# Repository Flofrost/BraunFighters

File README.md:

# GraphixCard

## Liscence

    This project is open source and open hardware, feel free too copy, edit, redistribute, and do whatever you want with it.
    I am not well versed in liscences, i just want to share my project.
    If you do use my project as a base for your work, please mention it.  :) 

## Info

    - Grahics card based on a ATMEGA1284.
    - Generates a PAL signal with 8 bit color.
    - Has a limited but expandable 3 voice synth (can add up to 3 voices).
    - Includes RS232 debugger (by that i mean it has an available RS232 port, it's up to anyone to do whatever).
    - C++ Code, compiled with avr-gcc and uploaded with avedude (using avriskmkii).
    - Electrical schematic made with Kicad.

## Objective

    - Make a funny retro video game.
    - This is the "video" part of the video game.
    - Make simple tools to program on the GraphiX Card.
    - Make a complete and handy instruction table.
    - Learn a ton about coding and electronics.

## About

    This project was brought to you by Florian Ballager, aka Flofrost.
## Braun Fighters

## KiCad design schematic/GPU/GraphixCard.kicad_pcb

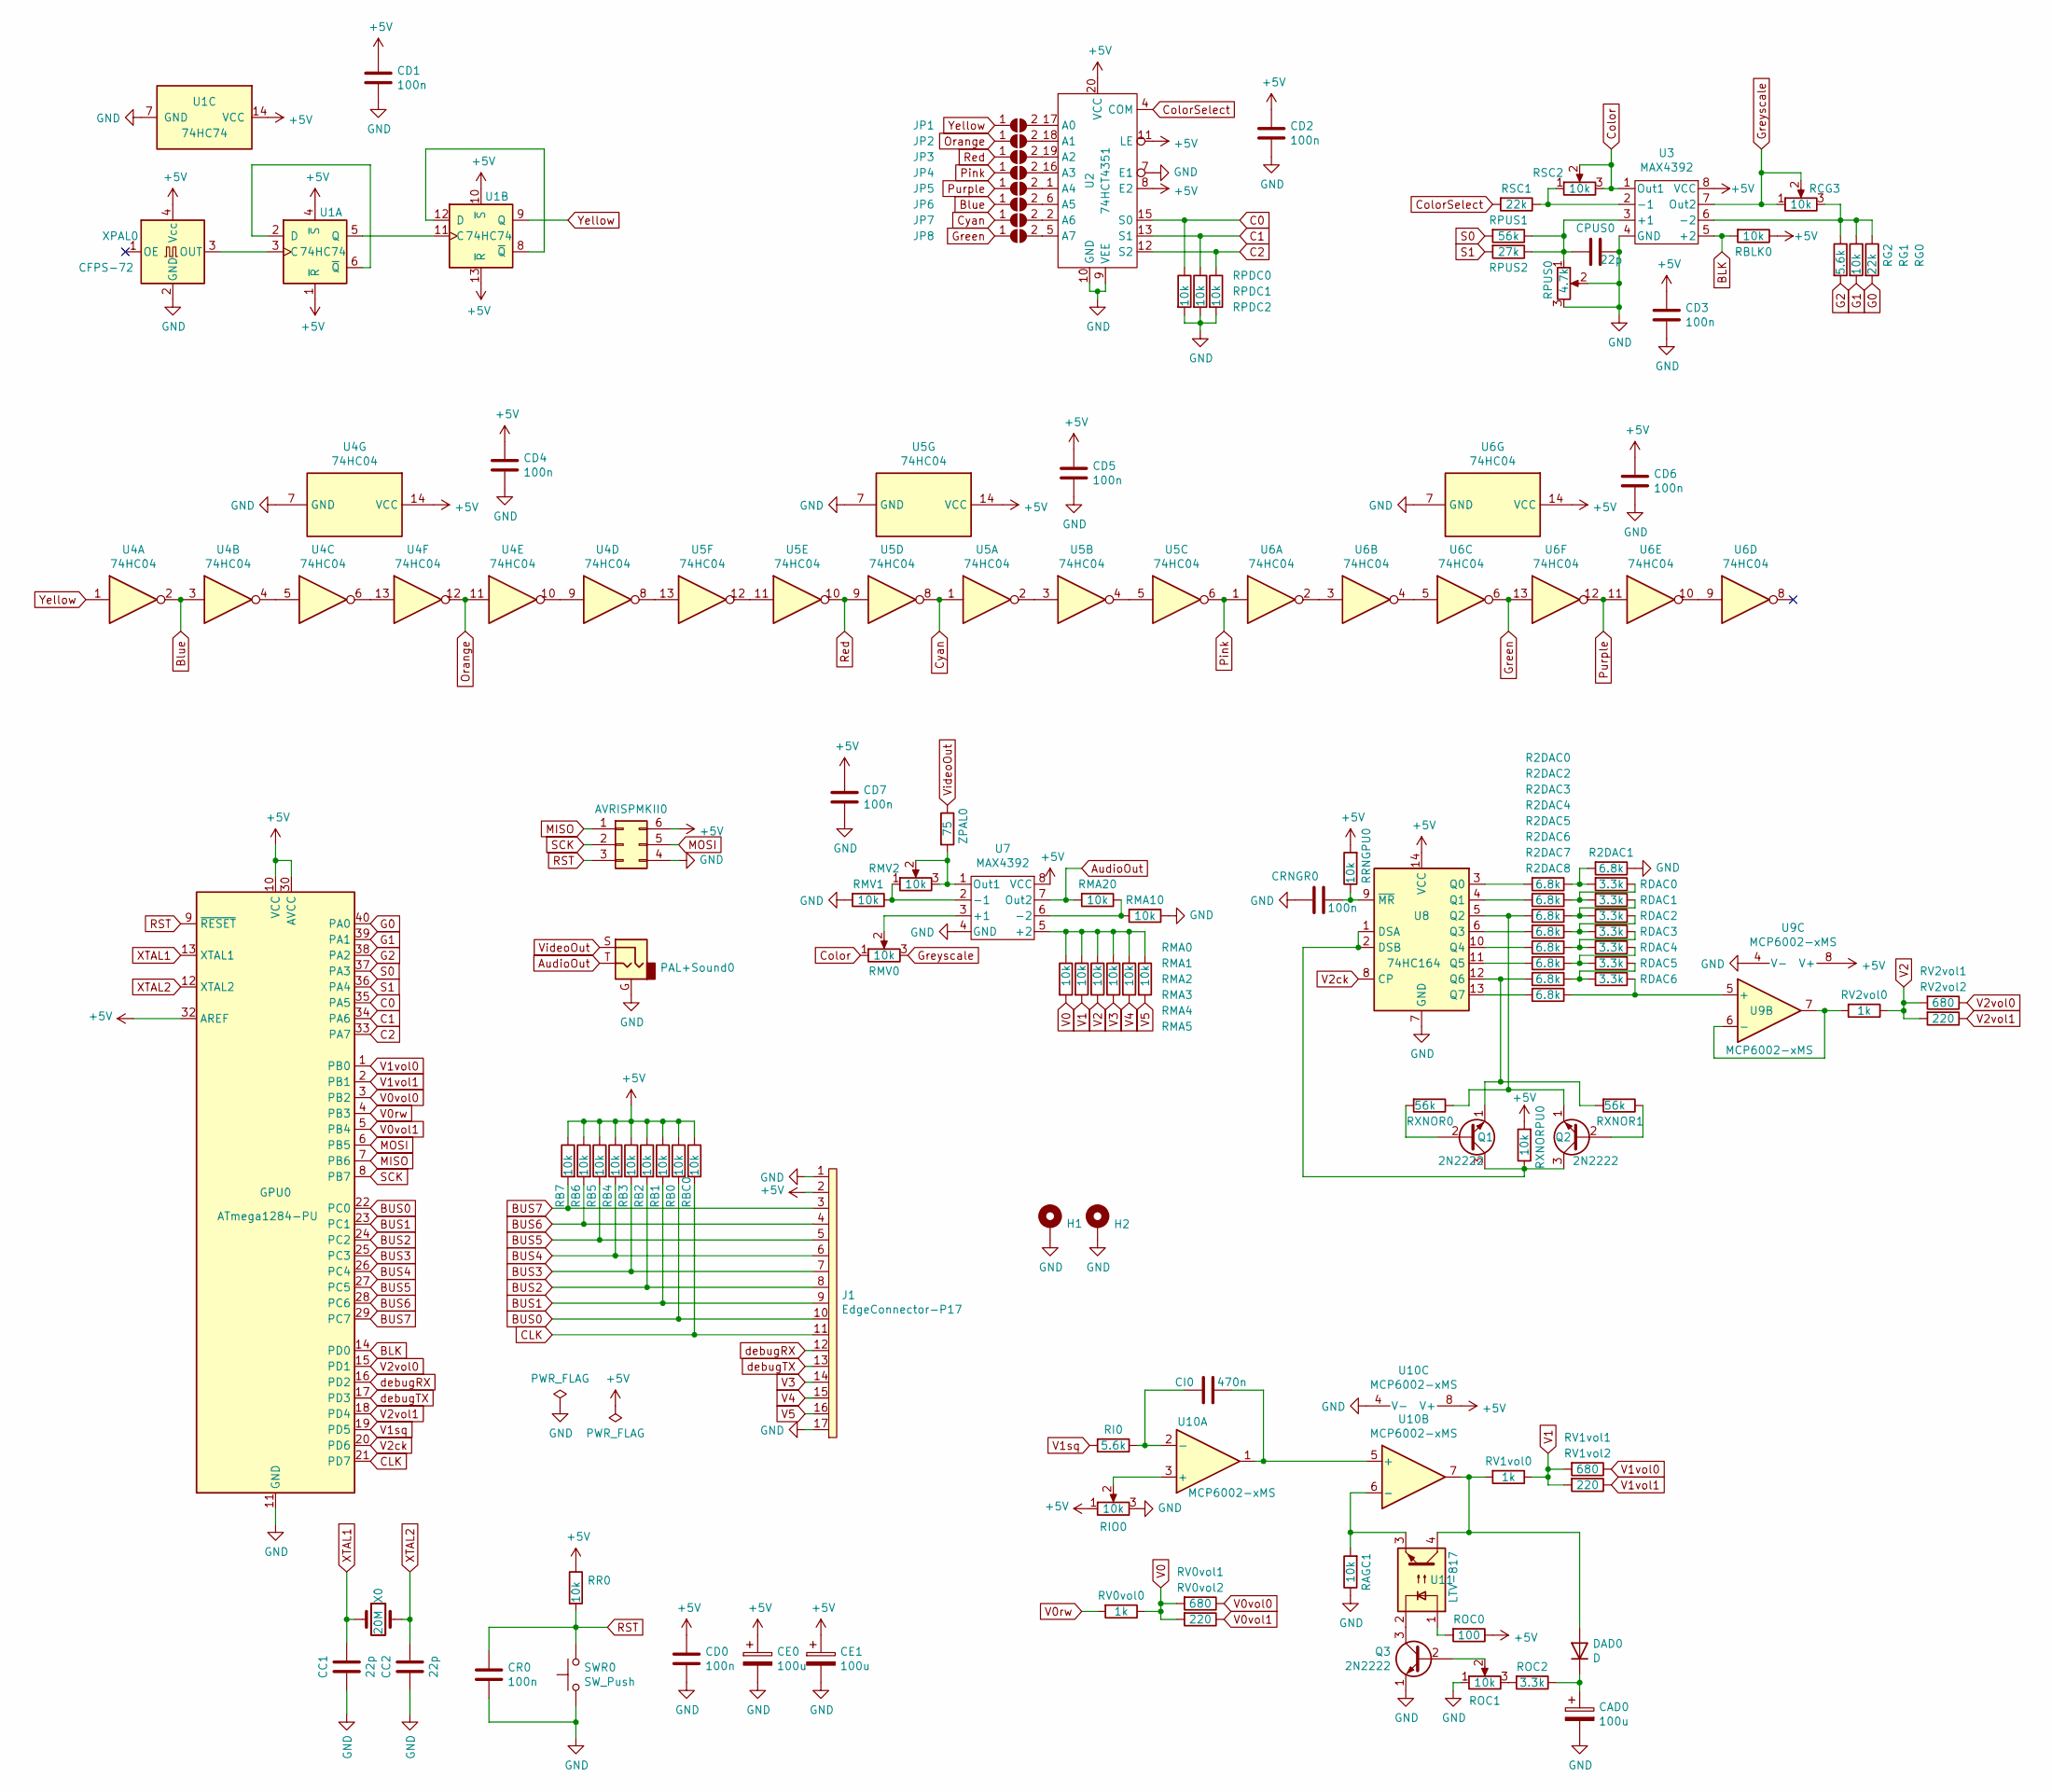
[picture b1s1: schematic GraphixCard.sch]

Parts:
AVRISPMKII0: Conn_02x03_Counter_Clockwise; PinSocket_2x03_P2.54mm_Vertical
CAD0: 100u; CP_Radial_D5.0mm_P2.00mm
CC1, CC2: 22p; C_Disc_D3.0mm_W1.6mm_P2.50mm
CD0, CD1, CD2, CD3, CD4, CD5, CD6, CD7: 100n; C_0805_2012Metric
CE0, CE1: 100u; CP_Radial_D5.0mm_P2.00mm
CI0: 470n; C_Rect_L7.0mm_W3.5mm_P5.00mm
CPUS0: 22p; C_Disc_D3.0mm_W1.6mm_P2.50mm
CR0: 100n; C_0805_2012Metric
CRNGR0: 100n; C_0805_2012Metric
DAD0: D; D_DO-34_SOD68_P7.62mm_Horizontal
GPU0: ATmega1284-PU; DIP-40_W15.24mm
H1, H2: MountingHole_Pad; MountingHole_3mm_Pad
J1: EdgeConnector-P17; EdgeConnector-P17-D8.00mm-P2.54mm
JP1, JP2, JP3, JP4, JP5, JP6, JP7, JP8: SolderJumper_2_Open; SolderJumper-2_P1.3mm_Open_RoundedPad1.0x1.5mm
PAL+Sound0: AudioJack2_Ground; GEII_Audio_Jack
Q1, Q2, Q3: 2N2222; SOT-23
R2DAC0, R2DAC1, R2DAC2, R2DAC3, R2DAC4, R2DAC5, R2DAC6, R2DAC7, R2DAC8: 6.8k; R_0805_2012Metric
RAGC1: 10k; R_0805_2012Metric
RB0, RB1, RB2, RB3, RB4, RB5, RB6, RB7: 10k; R_0805_2012Metric
RBC0: 10k; R_0805_2012Metric
RBLK0: 10k; R_0805_2012Metric
RCG3: 10k; Potentiometer_Piher_PT-10-V10_Vertical
RDAC0, RDAC1, RDAC2, RDAC3, RDAC4, RDAC5, RDAC6: 3.3k; R_0805_2012Metric
RG0: 22k; R_0805_2012Metric
RG1: 10k; R_0805_2012Metric
RG2: 5.6k; R_0805_2012Metric
RI0: 5.6k; R_0805_2012Metric
RIO0: 10k; Potentiometer_Vishay_T73YP_Vertical
RMA0, RMA1, RMA2, RMA3, RMA4, RMA5, RMA10, RMA20: 10k; R_0805_2012Metric
RMV0, RMV2: 10k; Potentiometer_Piher_PT-10-V10_Vertical
RMV1: 10k; R_0805_2012Metric
ROC0: 100; R_0805_2012Metric
ROC1: 10k; Potentiometer_Bourns_TC33X_Vertical
ROC2: 3.3k; R_0805_2012Metric
RPDC0, RPDC1, RPDC2: 10k; R_0805_2012Metric
RPUS0: 4.7k; Potentiometer_Piher_PT-10-V10_Vertical
RPUS1: 56k; R_0805_2012Metric
RPUS2: 27k; R_0805_2012Metric
RR0: 10k; R_0805_2012Metric
RRNGPU0: 10k; R_0805_2012Metric
RSC1: 22k; R_0805_2012Metric
RSC2: 10k; Potentiometer_Piher_PT-10-V10_Vertical
RV0vol0, RV1vol0, RV2vol0: 1k; R_0805_2012Metric
RV0vol1, RV1vol1, RV2vol1: 680; R_0805_2012Metric
RV0vol2, RV1vol2, RV2vol2: 220; R_0805_2012Metric
RXNOR0, RXNOR1: 56k; R_0805_2012Metric
RXNORPU0: 10k; R_0805_2012Metric
SWR0: SW_Push; SW_PUSH_6mm
U1: 74HC74; DIP-14_W7.62mm
U2: 74HCT4351; DIP-20_W7.62mm
U3, U7: MAX4392; OnSemi_Micro8
U4, U5, U6: 74HC04; DIP-14_W7.62mm
U8: 74HC164; DIP-14_W7.62mm
U9, U10: MCP6002-xMS; SOIC-8_3.9x4.9mm_P1.27mm
U11: LTV-817; DIP-4_W7.62mm
X0: 20M; Resonator-2Pin_W10.0mm_H5.0mm
XPAL0: CFPS-72; Oscillator_SMD_EuroQuartz_XO91-4Pin_7.0x5.0mm
ZPAL0: 75; R_0805_2012Metric

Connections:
+5V: AVRISPMKII0.6, CD0.1, CD1.1, CD2.1, CD3.1, CD4.1, CD5.1, CD6.1, CD7.1, CE0.1, CE1.1, GPU0.10 (VCC), GPU0.30 (AVCC), GPU0.32 (AREF), J1.2, RB0.1, RB1.1, RB2.1, RB3.1, RB4.1, RB5.1, RB6.1, RB7.1, RBC0.1, RBLK0.1, RIO0.1, ROC0.1, RR0.1, RRNGPU0.2, RXNORPU0.2, U1.1 (~R), U1.4 (~S), U1.10 (~S), U1.13 (~R), U1.14 (VCC), U2.8 (E2), U2.11 (LE), U2.20 (VCC), U3.8 (VCC), U4.14 (VCC), U5.14 (VCC), U6.14 (VCC), U7.8 (VCC), U8.14 (VCC), U9.8 (V+), U10.8 (V+), XPAL0.4 (Vcc)
AudioOut: PAL+Sound0.T, RMA20.2, U7.7 (Out2)
BLK: GPU0.14 (PD0), RBLK0.2, U3.5 (+2)
BUS0: GPU0.22 (PC0), J1.10, RB0.2
BUS1: GPU0.23 (PC1), J1.9, RB1.2
BUS2: GPU0.24 (PC2), J1.8, RB2.2
BUS3: GPU0.25 (PC3), J1.7, RB3.2
BUS4: GPU0.26 (PC4), J1.6, RB4.2
BUS5: GPU0.27 (PC5), J1.5, RB5.2
BUS6: GPU0.28 (PC6), J1.4, RB6.2
BUS7: GPU0.29 (PC7), J1.3, RB7.2
Blue: JP6.1 (A), U4.2, U4.3
C0: GPU0.35 (PA5), RPDC0.1, U2.15 (S0)
C1: GPU0.34 (PA6), RPDC1.1, U2.13 (S1)
C2: GPU0.33 (PA7), RPDC2.1, U2.12 (S2)
CLK: GPU0.21 (PD7), J1.11, RBC0.2
Color: RMV0.1, RSC2.2, RSC2.3, U3.1 (Out1)
ColorSelect: RSC1.2, U2.4 (COM)
Cyan: JP7.1 (A), U5.1, U5.8
G0: GPU0.40 (PA0), RG0.2
G1: GPU0.39 (PA1), RG1.2
G2: GPU0.38 (PA2), RG2.2
GND: AVRISPMKII0.4, CAD0.2, CC1.2, CC2.2, CD0.2, CD1.2, CD2.2, CD3.2, CD4.2, CD5.2, CD6.2, CD7.2, CE0.2, CE1.2, CPUS0.1, CR0.2, CRNGR0.2, GPU0.11 (GND), GPU0.31 (GND), H1.1, H2.1, J1.1, J1.17, PAL+Sound0.G, Q3.1 (E), R2DAC1.1, RAGC1.1, RIO0.3, RMA10.1, RMV1.2, ROC1.1, RPDC0.2, RPDC1.2, RPDC2.2, RPUS0.2, RPUS0.3, SWR0.1, U1.7 (GND), U2.7 (E1), U2.9 (VEE), U2.10 (GND), U3.4 (GND), U4.7 (GND), U5.7 (GND), U6.7 (GND), U7.4 (GND), U8.7 (GND), U9.4 (V-), U10.4 (V-), XPAL0.2 (GND)
Green: JP8.1 (A), U6.6, U6.13
Greyscale: RCG3.1, RCG3.2, RMV0.3, U3.7 (Out2)
MISO: AVRISPMKII0.1, GPU0.7 (PB6)
MOSI: AVRISPMKII0.5, GPU0.6 (PB5)
unnamed: CAD0.1, DAD0.1 (K), ROC2.1
unnamed: CI0.1, U10.1, U10.5 (+)
unnamed: CI0.2, RI0.1, U10.2 (-)
unnamed: CPUS0.2, RPUS0.1, RPUS1.1, RPUS2.1, U3.3 (+1)
unnamed: CRNGR0.1, RRNGPU0.1, U8.9 (~MR)
unnamed: DAD0.2 (A), RV1vol0.2, U10.7, U11.4
unnamed: JP1.2 (B), U2.17 (A0)
unnamed: JP2.2 (B), U2.18 (A1)
unnamed: JP3.2 (B), U2.19 (A2)
unnamed: JP4.2 (B), U2.16 (A3)
unnamed: JP5.2 (B), U2.1 (A4)
unnamed: JP6.2 (B), U2.6 (A5)
unnamed: JP7.2 (B), U2.2 (A6)
unnamed: JP8.2 (B), U2.5 (A7)
unnamed: Q1.1 (E), R2DAC7.2, RXNOR1.2, U8.12 (Q6)
unnamed: Q1.2 (B), RXNOR0.2
unnamed: Q1.3 (C), Q2.3 (C), RXNORPU0.1, U8.1 (DSA), U8.2 (DSB)
unnamed: Q2.1 (E), R2DAC3.2, RXNOR0.1, U8.5 (Q2)
unnamed: Q2.2 (B), RXNOR1.1
unnamed: Q3.2 (B), ROC1.2
unnamed: Q3.3 (C), U11.2
unnamed: R2DAC0.1, R2DAC1.2, RDAC0.2
unnamed: R2DAC0.2, U8.3 (Q0)
unnamed: R2DAC2.1, RDAC0.1, RDAC1.2
unnamed: R2DAC2.2, U8.4 (Q1)
unnamed: R2DAC3.1, RDAC1.1, RDAC2.2
unnamed: R2DAC4.1, RDAC2.1, RDAC3.2
unnamed: R2DAC4.2, U8.6 (Q3)
unnamed: R2DAC5.1, RDAC3.1, RDAC4.2
unnamed: R2DAC5.2, U8.10 (Q4)
unnamed: R2DAC6.1, RDAC4.1, RDAC5.2
unnamed: R2DAC6.2, U8.11 (Q5)
unnamed: R2DAC7.1, RDAC5.1, RDAC6.2
unnamed: R2DAC8.1, RDAC6.1, U9.5 (+)
unnamed: R2DAC8.2, U8.13 (Q7)
unnamed: RAGC1.2, U10.6 (-), U11.3
unnamed: RCG3.3, RG0.1, RG1.1, RG2.1, U3.6 (-2)
unnamed: RIO0.2, U10.3 (+)
unnamed: RMA0.1, RMA1.1, RMA2.1, RMA3.1, RMA4.1, RMA5.1, U7.5 (+2)
unnamed: RMA10.2, RMA20.1, U7.6 (-2)
unnamed: RMV0.2, U7.3 (+1)
unnamed: RMV1.1, RMV2.1, U7.2 (-1)
unnamed: RMV2.2, RMV2.3, U7.1 (Out1), ZPAL0.2
unnamed: ROC0.2, U11.1
unnamed: ROC1.3, ROC2.2
unnamed: RSC1.1, RSC2.1, U3.2 (-1)
unnamed: RV2vol0.2, U9.6 (-), U9.7
unnamed: U1.2 (D), U1.6 (~Q)
unnamed: U1.3 (C), XPAL0.3 (OUT)
unnamed: U1.5 (Q), U1.11 (C)
unnamed: U1.8 (~Q), U1.12 (D)
unnamed: U4.4, U4.5
unnamed: U4.8, U5.13
unnamed: U4.9, U4.10
unnamed: U4.6, U4.13
unnamed: U5.2, U5.3
unnamed: U5.4, U5.5
unnamed: U5.11, U5.12
unnamed: U6.2, U6.3
unnamed: U6.4, U6.5
unnamed: U6.9, U6.10
Orange: JP2.1 (A), U4.11, U4.12
Pink: JP4.1 (A), U5.6, U6.1
Purple: JP5.1 (A), U6.11, U6.12
RST: AVRISPMKII0.3, CR0.1, GPU0.9 (~RESET), RR0.2, SWR0.2
Red: JP3.1 (A), U5.9, U5.10
S0: GPU0.37 (PA3), RPUS1.2
S1: GPU0.36 (PA4), RPUS2.2
SCK: AVRISPMKII0.2, GPU0.8 (PB7)
V0: RMA0.2, RV0vol0.1, RV0vol1.2, RV0vol2.2
V0rw: GPU0.4 (PB3), RV0vol0.2
V0vol0: GPU0.3 (PB2), RV0vol1.1
V0vol1: GPU0.5 (PB4), RV0vol2.1
V1: RMA1.2, RV1vol0.1, RV1vol1.2, RV1vol2.2
V1sq: GPU0.19 (PD5), RI0.2
V1vol0: GPU0.1 (PB0), RV1vol1.1
V1vol1: GPU0.2 (PB1), RV1vol2.1
V2: RMA2.2, RV2vol0.1, RV2vol1.2, RV2vol2.2
V2ck: GPU0.20 (PD6), U8.8 (CP)
V2vol0: GPU0.15 (PD1), RV2vol1.1
V2vol1: GPU0.18 (PD4), RV2vol2.1
V3: J1.14, RMA3.2
V4: J1.15, RMA4.2
V5: J1.16, RMA5.2
VideoOut: PAL+Sound0.S, ZPAL0.1
XTAL1: CC1.1, GPU0.13 (XTAL1), X0.1
XTAL2: CC2.1, GPU0.12 (XTAL2), X0.2
Yellow: JP1.1 (A), U1.9 (Q), U4.1
debugRX: GPU0.16 (PD2), J1.12
debugTX: GPU0.17 (PD3), J1.13

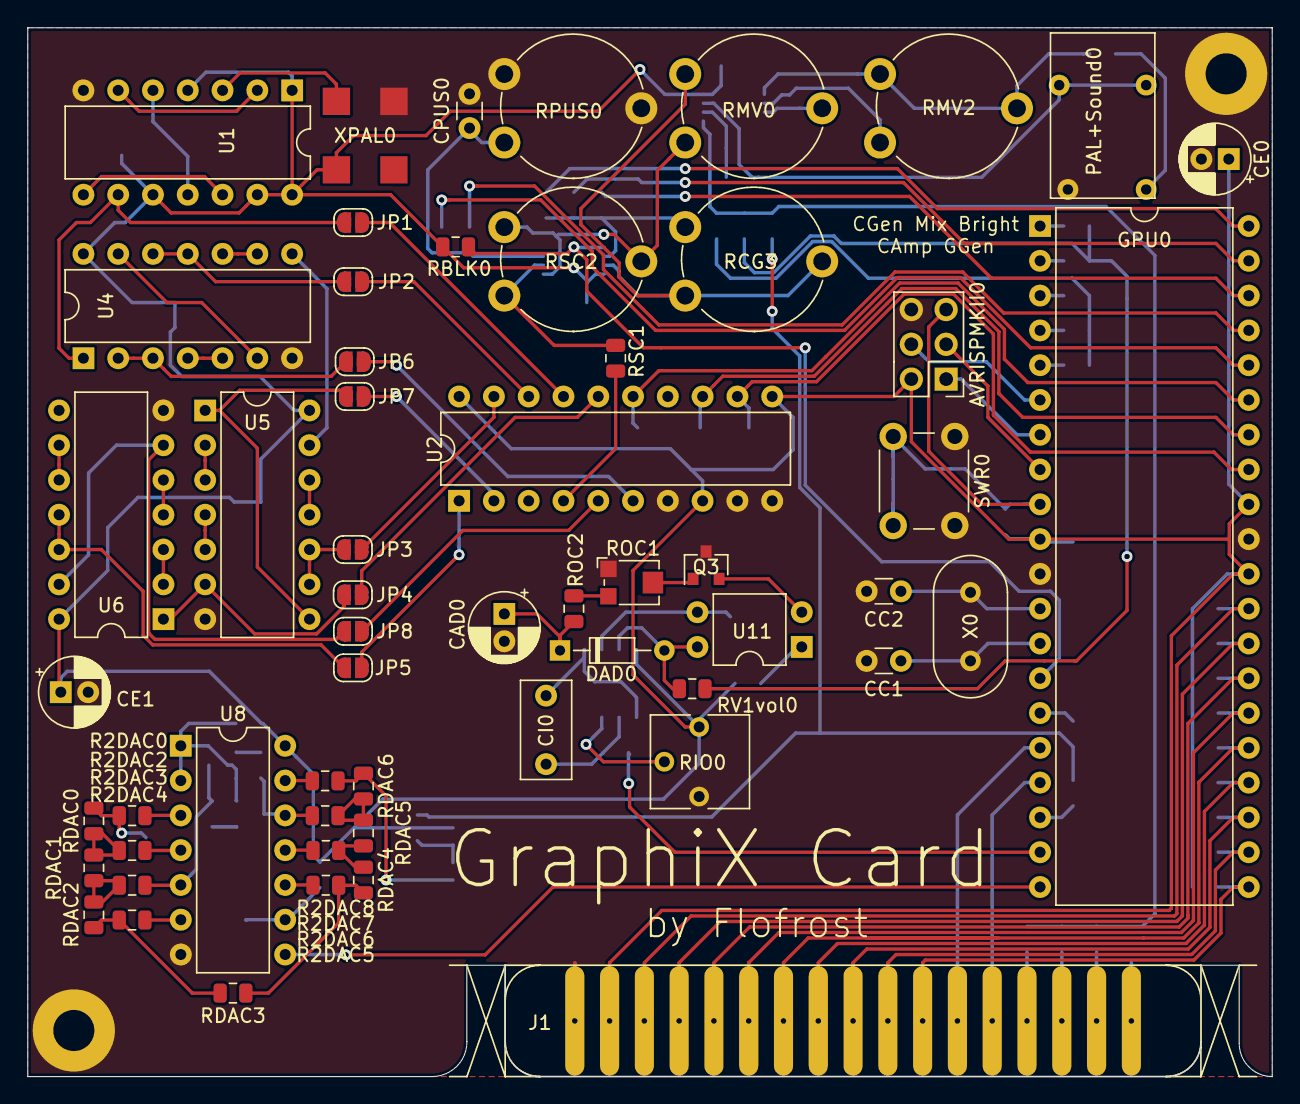
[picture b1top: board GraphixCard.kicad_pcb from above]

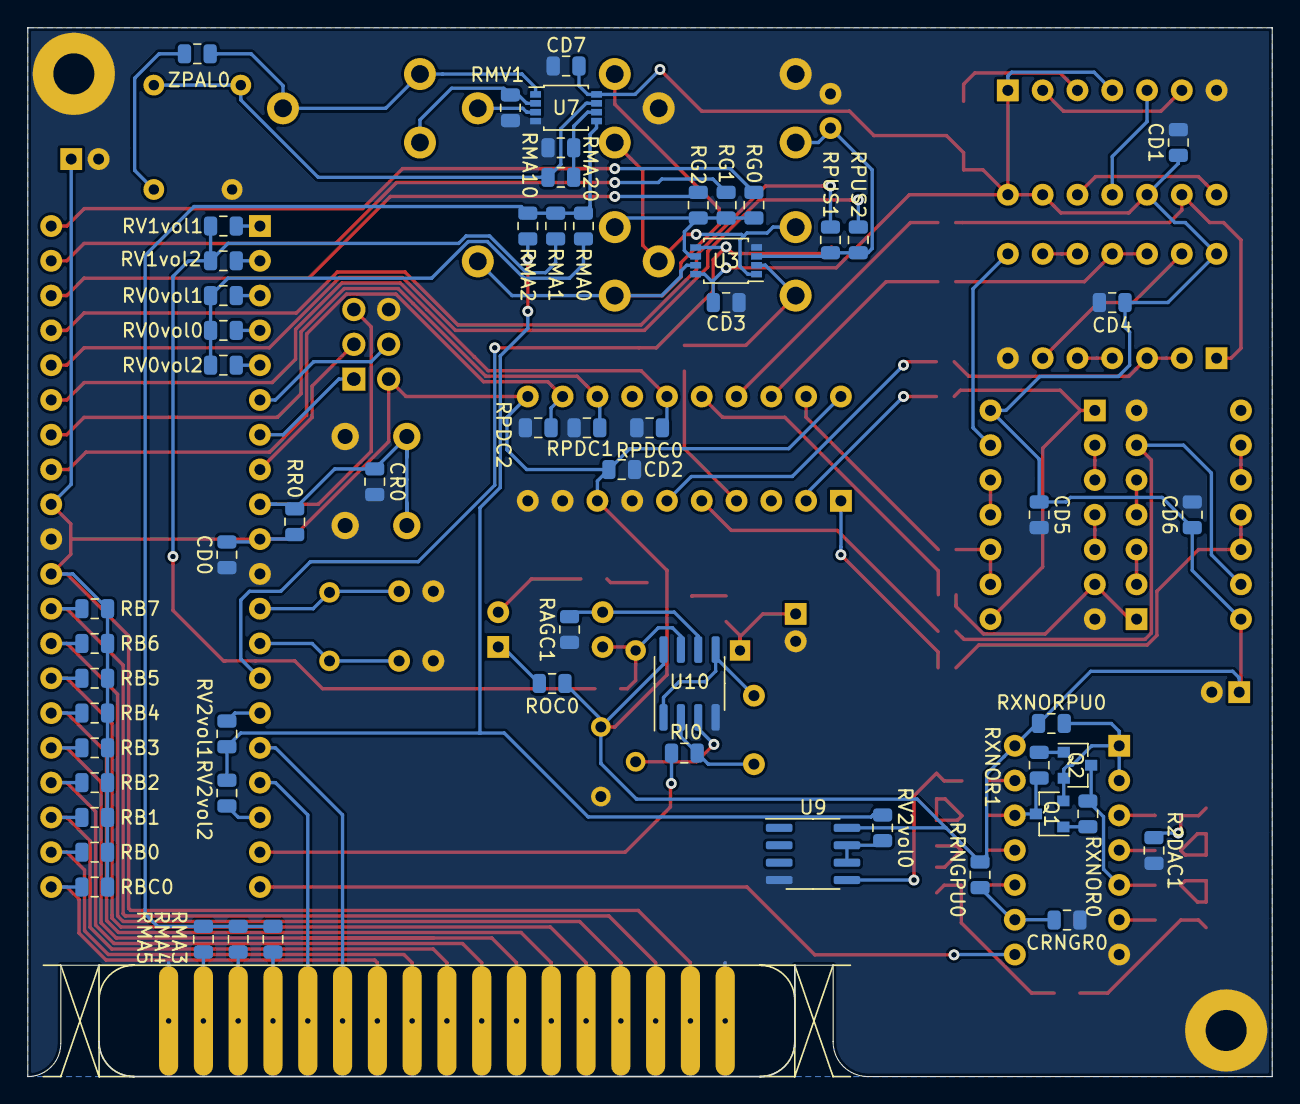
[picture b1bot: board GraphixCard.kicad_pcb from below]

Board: 2 copper layers, 90.9 x 76.6 mm, 119 parts (60 on the bottom side), 117 nets.

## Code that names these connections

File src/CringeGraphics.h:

#ifndef CRINGEGRAPHICS_H
#define CRINGEGRAPHICS_H   

#include <avr/pgmspace.h>

//#define GREYSCALE

#define WIDTH 120
#define HEIGHT 120
#define TOTALPIXELS 14400
#define START_FRAME 28
#define INCLINE 40

#define FPORCH 0
#define START_BURST 1
#define STOP_BURST 2
#define DRAW_LINE 3

#define TIMING_STOP_HSYNC 15
#define TIMING_START_DRAW_LINE 40

#define clkF() DDRD |= 0x80
#define clkR() DDRD &= 0x7F
#define CLK  (PIND & 0x80)
#define BUSR     PINC
#define BUSW(x)  DDRC = ~(x)


extern volatile uint16_t lineCounter;
extern volatile uint8_t done, vsync, can_draw, enabled;
extern volatile uint8_t line, state, stack[256], stack_length;
extern uint8_t frame[HEIGHT][WIDTH];

extern const uint8_t BURST;

extern const uint8_t BLACK;
extern const uint8_t WHITE;
extern const uint8_t GREY;

extern const uint8_t YELLOW;
extern const uint8_t ORANGE;
extern const uint8_t RED;
extern const uint8_t PINK;
extern const uint8_t PURPLE;
extern const uint8_t BLUE;
extern const uint8_t CYAN;
extern const uint8_t GREEN;

extern const uint8_t EDGE;


#ifdef DEBUG
#include <stdio.h>
void debugSendd(const uint8_t x);
void debugSends(const char* s);
#endif

#define CAN_CALCULATE (!can_draw)

//Asks CPU for stack
void fetchStack();

//enables display, disabling display yields display time to calculations
void setEnabled(const uint8_t ena);
//Fills the whole screen with a color.
void fillScreen(const uint8_t color);
//Adds a value to each pixel.
void addScreen(const char amount);
//Shifts the whole screen to the right by an amount.
void rShiftScreen();
//Shifts the whole screen to the left by an amount.
void lShiftScreen();
//Shifts the whole screen upwards by an amount.
void uShiftScreen();
//Shifts the whole screen downwards by an amount.
void dShiftScreen();
//Draws an orthonormal grid across the screen
void drawGrid(const uint8_t x, const uint8_t y, const uint8_t color);
//Changes a single pixel
void setPixel(const uint8_t x, const uint8_t y, const uint8_t color);
//Draws a horizontal line.
void drawHLine(const uint8_t line, const uint8_t start, const uint8_t end, const uint8_t color);
//Draws a vertical line.
void drawVLine(const uint8_t column, const uint8_t start, const uint8_t end, const uint8_t color);
//Draw any line.
void drawLine(const uint8_t x1, const uint8_t y1, const uint8_t x2, const uint8_t y2, const uint8_t color);
//Draws a hollow rectangle.
void drawRect(const uint8_t xs, const uint8_t ys, const uint8_t xe, const uint8_t ye, const uint8_t color);
//Draws a filled rectangle.
void drawFRect(const uint8_t xs, const uint8_t ys, const uint8_t xe, const uint8_t ye, const uint8_t color);
//Draws a regular polygon
void drawRPoly(const uint8_t xc, const uint8_t yc, const uint8_t radius, const uint8_t edges, const uint8_t angleOffset, const uint8_t color);
//Draws a filled regular polygon
void drawRFPoly(const uint8_t xc, const uint8_t yc, const uint8_t radius, const uint8_t edges, const uint8_t angleOffset, const uint8_t color);
//Draws a polygon following the points given
void drawPoly(const uint8_t edges, const uint8_t color, const uint8_t* points);
//Draws a filled polygon following the points given
void drawFPoly(const uint8_t edges, const uint8_t color, const uint8_t* points);
//Draws a segmented line, points are structured as follow: [x0,y0,x1,y1,x2,y2,x3,y3,x4,y4...]
void drawKinkLine(const uint8_t length, const uint8_t color, const uint8_t* points);
//Draws a character
void drawChar(const uint8_t x, const uint8_t y, const char c, const uint8_t color);
//Draws a string of characters, returns length of printed string
uint8_t drawString(const uint8_t xs, const uint8_t ys, const char* s, const uint8_t color);
//Draws a sprite
void drawSprite(const uint8_t x, const uint8_t y, const uint8_t spritID, const uint8_t options);

//Colors inside a shape using the edge fake color
void colorIn(const uint8_t x1, const uint8_t y1, const uint8_t x2, const uint8_t y2, const uint8_t color);


#define guess_prescaler0(note) (((note) < 15) ? 5 :(\
                               ((note) < 39) ? 4 : 3))

#define guess_prescaler2(note) (((note) < 15) ? 7 :(\
                               ((note) < 27) ? 6 :(\
                               ((note) < 39) ? 5 : 4)))

#define setupVoice0()   TCCR0A = 0x42;\
                        DDRB |= 1<<PB3

void changeVoice0(const uint8_t tone);

#define setupVoice1()   TCCR1A = 0x40;\
                        TCCR1B = 0x08;\
                        DDRD |= 1<<PD5

void changeVoice1(const uint8_t tone);

#define setupVoice2()   TCCR2A = 0x12;\
                        DDRD |= (1<<PD6)

void changeVoice2(const uint8_t tone);


#endif

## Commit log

2021-07-13 Clean up
2021-07-13 Added some ideas in mind map
2021-08-03 added music folder
2021-08-03 Added main theme :)
2021-08-03 renamed files
2021-08-03 removed test folder for the music
2021-08-03 added idead file
2021-08-03 Started on new theme
2021-08-03 Worked one sashas theme
2021-08-04 Worked on sashatheme and started a new piece
2021-08-04 Renamed some files
2021-08-05 moved all music data to the CPU (aka here)
2021-08-05 Worked on some pieces and added a new piece
2021-08-31 rick roll
2021-11-13 COmmunication Protocol WIP
2021-12-23 Communication Protocol reset, need to rethink it
2021-12-24 Window display working! Using CImg library
2021-12-25 Working Display System!!
2021-12-27 Made small env to simulate GPU
2022-02-11 Changed stack communication through file
2022-02-13 need to fix terminated by signal unknown
2022-02-24 Communication Works!!! Can send instruction!!
2022-02-24 Made cpu's drawing functions, to write on stack
2022-02-27 Working on new piece, is partially complete :)
2022-02-27 Finished Calm7
2022-03-22 Fused repo with CringeGraphics (formerly GraphiX)
